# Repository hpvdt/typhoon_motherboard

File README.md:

# Typhoon Motherboard

General template repository for our hardware projects, especially one-off and self-contained projects like custom test equipment. This template assumes that the hardware is being designed in KiCad.

## Organization

Pretty self-explanitory, put hardware related files into the `hardware` folder, firmware in the `firmware` folder. Other folders can be added as needed: for example a `media` folder is handy for storing pictures related to a project which can be used in documentation.

## Conventions

Partly for consistency, partly for functionality; please follow the following conventions:

- Try to keep folder names to single words and all lowercase
- Use underscores to separate words in names (e.g. `board_rev1`). **DO NOT USE SPACES! ESPECIALLY FOR FOLDERS CONTAINING CODE!** Spaces in file paths may cause issues in compilers and such so best to avoid them entirely.

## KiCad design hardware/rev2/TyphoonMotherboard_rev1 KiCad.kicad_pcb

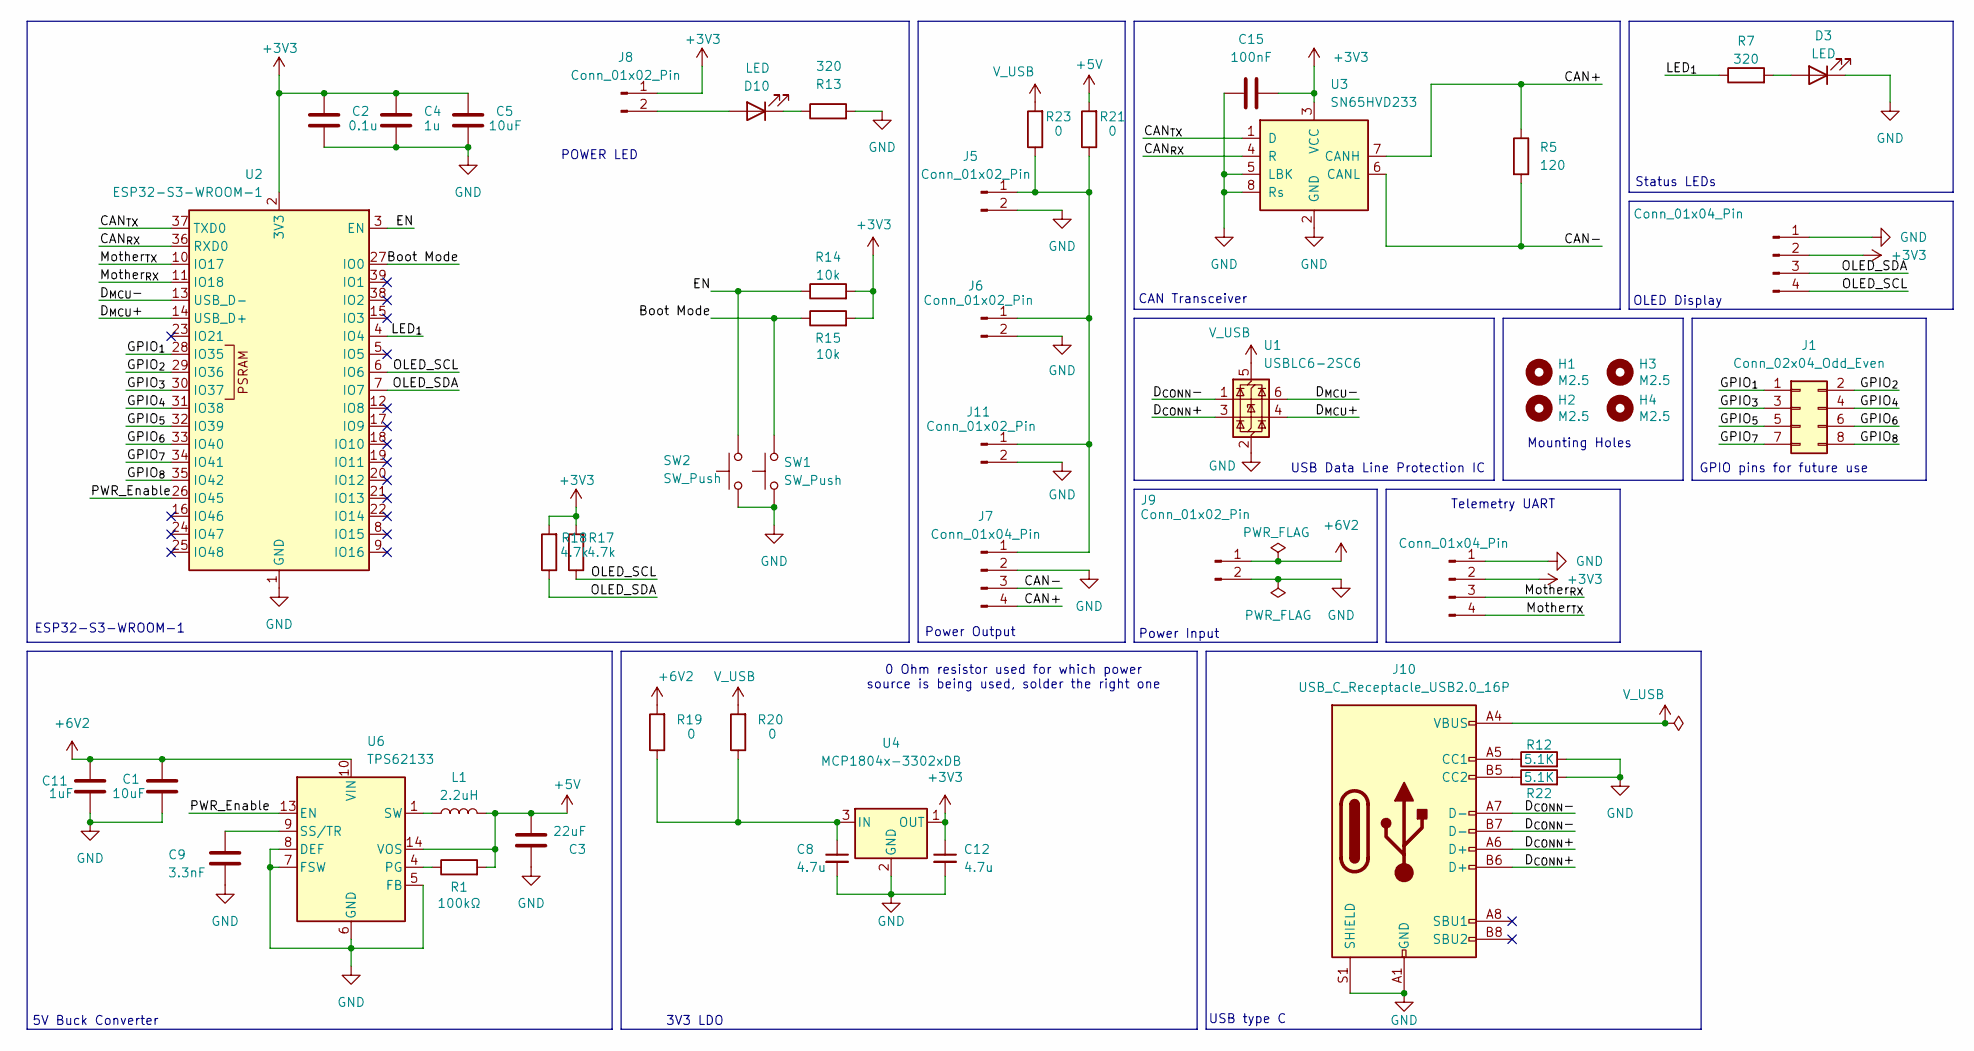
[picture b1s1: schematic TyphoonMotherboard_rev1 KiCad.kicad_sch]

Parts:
C1: 10uF; C_0603_1608Metric
C2: 0.1u; C_0603_1608Metric; Manufacturer Part Number CL10B105KP8NNNC
C3: 22uF; C_0603_1608Metric
C4: 1u; C_0603_1608Metric; Manufacturer Part Number C0603C104K5RACTU
C5: 10uF; C_0603_1608Metric; Manufacturer Part Number CL10A106KQ8NNNC
C8, C12: 4.7u; C_0603_1608Metric; LCSC C1779
C9: 3.3nF; C_0603_1608Metric
C11: 1uF; C_0603_1608Metric
C15: 100nF; C_0603_1608Metric; Manufacturer Part Number CL10E104KC8VPNC
D3, D10: LED; LED_0805_2012Metric; Manufacturer Part Number LTST-C171GKT
H1, H2, H3, H4: M2.5; MountingHole_2.7mm_M2.5
J1: Conn_02x04_Odd_Even; PinSocket_2x04_P2.54mm_Vertical
J2, J4, J7: Conn_01x04_Pin; JST_XH_B4B-XH-A_1x04_P2.50mm_Vertical
J5, J6, J9, J11: Conn_01x02_Pin; JST_XH_B2B-XH-A_1x02_P2.50mm_Vertical
J8: Conn_01x02_Pin; PinHeader_1x02_P2.54mm_Vertical
J10: USB_C_Receptacle_USB2.0_16P; USB_C_Receptacle_JAE_DX07S016JA1R1500; Manufacturer Part Number DX07S016JA3R1500
L1: 2.2uH; L_0805_2012Metric
R1: 100kΩ; R_0603_1608Metric
R5: 120; R_0603_1608Metric
R7: 320; R_0603_1608Metric; Manufacturer Part Number RT0603DRE07320RL
R12, R22: 5.1K; R_0603_1608Metric; Manufacturer Part Number RC0603FR-075K1L
R13: 320; R_0603_1608Metric; Manufacturer Part Number ERA-3AEB331V
R14, R15: 10k; R_0603_1608Metric; Manufacturer Part Number RMCF0603JT10K0
R17, R18: 4.7k; R_0603_1608Metric; Manufacturer Part Number RMCF0603JT10K0
R19, R20, R21, R23: 0; R_1206_3216Metric; Manufacturer Part Number RMCF0603JT10K0
SW1, SW2: SW_Push; SMT_FS
U1: USBLC6-2SC6; SOT-23-6; Manufacturer Part Number USBLC6-2SC6; Digikey Part Number 497-5235-1-ND
U2: ESP32-S3-WROOM-1; Manufacturer Part Number ESP32-S3-WROOM-1-N4R8
U3: SN65HVD233; SOIC-8_3.9x4.9mm_P1.27mm; Manufacturer Part Number SN65HVD233DR
U4: MCP1804x-3302xDB; SOT-223-3_TabPin2
U6: TPS62133; VQFN-16-1EP_3x3mm_P0.5mm_EP1.68x1.68mm_ThermalVias

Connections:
+3V3: C2.1, C4.1, C5.1, C12.1, C15.2, J2.2, J4.2, J8.1, R14.2, R15.2, R17.2, R18.2, U2.2 (3V3), U3.3 (VCC), U4.1 (OUT)
+5V: C3.2, L1.2, R1.2, R21.2, U6.14 (VOS)
+6V2: C1.2, C11.2, J9.1, R19.2, U6.10 (VIN), U6.11 (VIN), U6.12 (VIN)
/Boot Mode: R15.1, SW1.2, U2.27 (IO0)
/CAN+: J7.4, R5.1, U3.7 (CANH)
/CAN-: J7.3, R5.2, U3.6 (CANL)
/CAN_{RX}: U2.36 (RXD0), U3.4 (R)
/CAN_{TX}: U2.37 (TXD0), U3.1 (D)
/D_{CONN}+: J10.A6 (D+), J10.B6 (D+), U1.3 (I/O2)
/D_{CONN}-: J10.A7 (D-), J10.B7 (D-), U1.1 (I/O1)
/D_{MCU}+: U1.4 (I/O2), U2.14 (USB_D+)
/D_{MCU}-: U1.6 (I/O1), U2.13 (USB_D-)
/EN: R14.1, SW2.2, U2.3 (EN)
/GPIO_{1}: J1.1, U2.28 (IO35)
/GPIO_{2}: J1.2, U2.29 (IO36)
/GPIO_{3}: J1.3, U2.30 (IO37)
/GPIO_{4}: J1.4, U2.31 (IO38)
/GPIO_{5}: J1.5, U2.32 (IO39)
/GPIO_{6}: J1.6, U2.33 (IO40)
/GPIO_{7}: J1.7, U2.34 (IO41)
/GPIO_{8}: J1.8, U2.35 (IO42)
/LED_{1}: R7.1, U2.4 (IO4)
/Mother_{RX}: J2.3, U2.11 (IO18)
/Mother_{TX}: J2.4, U2.10 (IO17)
/OLED_SCL: J4.4, R17.1, U2.6 (IO6)
/OLED_SDA: J4.3, R18.1, U2.7 (IO7)
/PWR_Enable: U2.26 (IO45), U6.13 (EN)
GND: C1.1, C2.2, C3.1, C4.2, C5.2, C8.2, C9.1, C11.1, C12.2, C15.1, D3.1 (K), J2.1, J4.1, J5.2, J6.2, J7.2, J9.2, J10.A1 (GND), J10.A12 (GND), J10.B1 (GND), J10.B12 (GND), J10.S1 (SHIELD), J11.2, R12.2, R13.2, R22.2, SW1.1, SW2.1, U1.2 (GND), U2.1 (GND), U2.40 (GND), U2.41 (GND), U3.2 (GND), U3.5 (LBK), U3.8 (Rs), U4.2 (GND), U6.5 (FB), U6.6 (GND), U6.7 (FSW), U6.8 (DEF), U6.15 (GND), U6.16 (GND), U6.17 (GND)
unnamed: D3.2 (A), R7.2
unnamed: D10.2 (A), J8.2
unnamed: D10.1 (K), R13.1
unnamed: J10.A5 (CC1), R12.1
unnamed: J10.B5 (CC2), R22.1
unnamed: J5.1, J6.1, J7.1, J11.1, R21.1, R23.1
unnamed: L1.1, U6.1 (SW), U6.2 (SW), U6.3 (SW)
unnamed: C8.1, R19.1, R20.1, U4.3 (IN)
unnamed: R1.1, U6.4 (PG)
unnamed: C9.2, U6.9 (SS/TR)
V_USB: J10.A4 (VBUS), J10.A9 (VBUS), J10.B4 (VBUS), J10.B9 (VBUS), R20.2, R23.2, U1.5 (VBUS)

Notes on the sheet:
Status LEDs
Power Input
ESP32-S3-WROOM-1
USB Data Line Protection IC
CAN Transceiver
5V Buck Converter
3V3 LDO
OLED Display
GPIO pins for future use
Mounting Holes
Power Output
POWER LED
0 Ohm resistor used for which power source is being used, solder the right one
USB type C
Telemetry UART

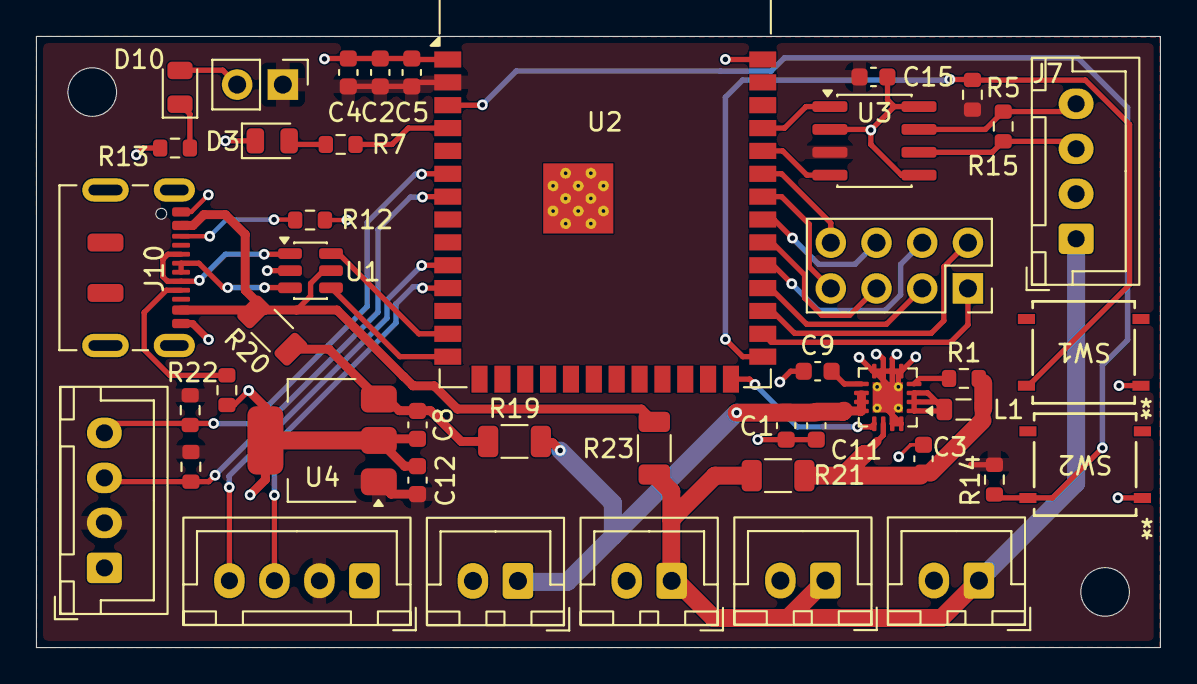
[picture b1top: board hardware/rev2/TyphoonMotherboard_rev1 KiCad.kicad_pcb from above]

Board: 2 copper layers, 62.4 x 33.9 mm, 48 parts (0 on the bottom side), 39 nets.

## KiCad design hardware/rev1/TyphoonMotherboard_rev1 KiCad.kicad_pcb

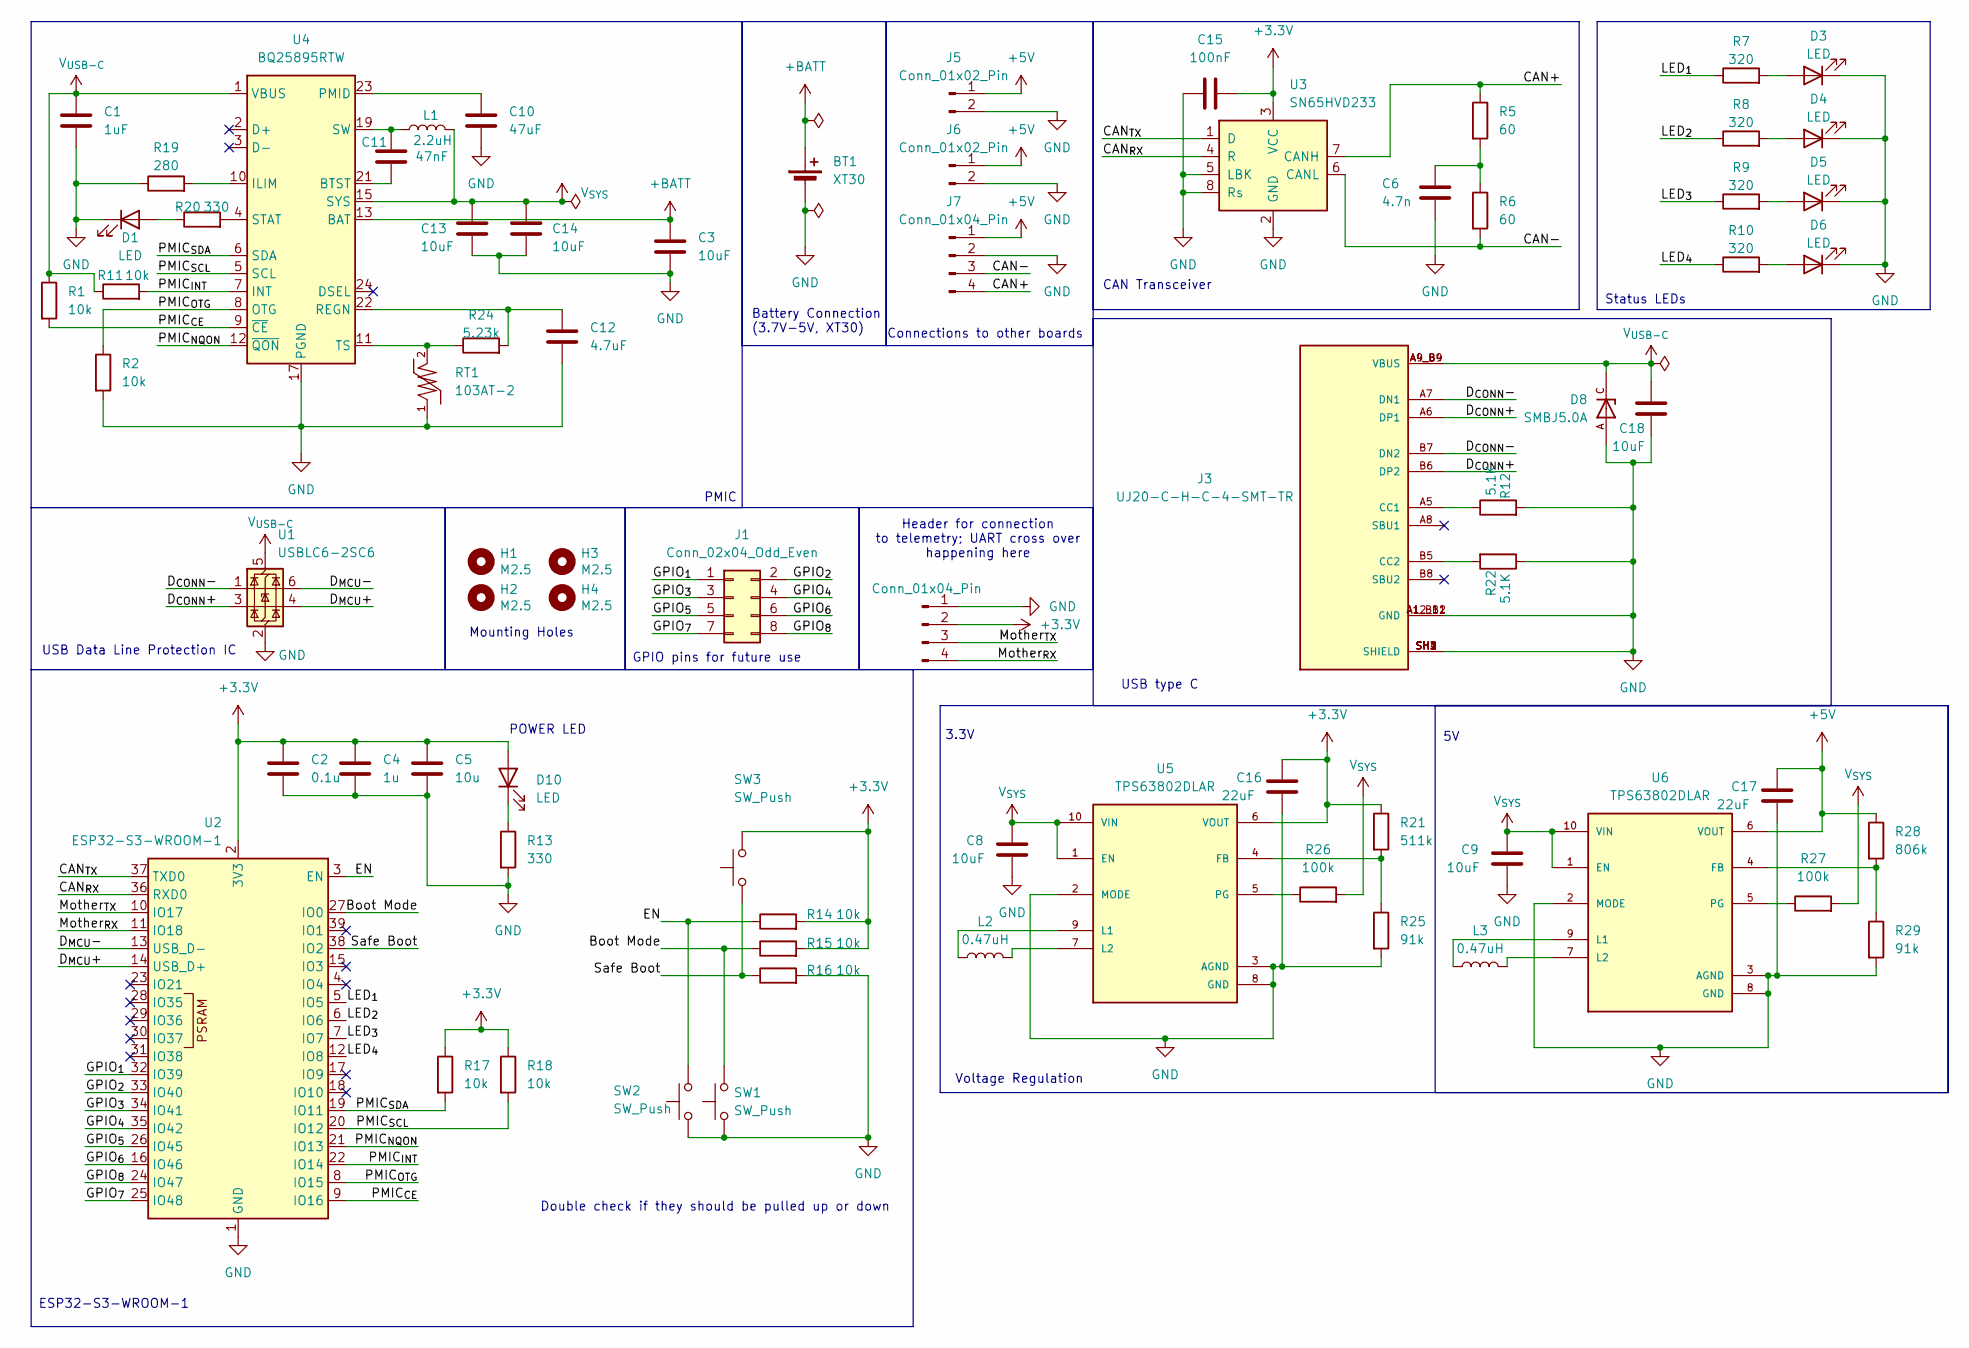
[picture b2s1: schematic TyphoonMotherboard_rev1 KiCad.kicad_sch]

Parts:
BT1: XT30; AMASS_XT30U-F_1x02_P5.0mm_Vertical
C1: 1uF; C_0603_1608Metric
C2: 0.1u; C_0603_1608Metric
C3, C8, C9, C13, C14, C18: 10uF; C_0603_1608Metric
C4: 1u; C_0603_1608Metric
C5: 10u; C_0603_1608Metric
C6: 4.7n; C_0603_1608Metric
C10: 47uF; C_0603_1608Metric
C11: 47nF; C_0603_1608Metric
C12: 4.7uF; C_0603_1608Metric
C15: 100nF; C_0603_1608Metric
C16, C17: 22uF; C_0603_1608Metric
D1, D3, D4, D5, D6, D10: LED; LED_0805_2012Metric
D8: SMBJ5.0A; DIOM4336X265N; PARTREV F2102
H1, H2, H3, H4: M2.5; MountingHole_2.7mm_M2.5
J1: Conn_02x04_Odd_Even; PinSocket_2x04_P2.54mm_Vertical
J2, J7: Conn_01x04_Pin; JST_XH_B4B-XH-A_1x04_P2.50mm_Vertical
J3: UJ20-C-H-C-4-SMT-TR; CUI_UJ20-C-H-C-4-SMT-TR; PARTREV 1.0
J5, J6: Conn_01x02_Pin; JST_XH_B2B-XH-A_1x02_P2.50mm_Vertical
L1: 2.2uH; L_0805_2012Metric
L2, L3: 0.47uH; L_0603_1608Metric
R1, R2, R11, R14, R15, R16, R17, R18: 10k; R_0603_1608Metric
R5, R6: 60; R_0603_1608Metric
R7, R8, R9, R10: 320; R_0603_1608Metric
R12, R22: 5.1K; R_0603_1608Metric
R13, R20: 330; R_0603_1608Metric
R19: 280; R_0603_1608Metric
R21: 511k; R_0603_1608Metric
R24: 5.23k; R_0603_1608Metric
R25, R29: 91k; R_0603_1608Metric
R26, R27: 100k; R_0603_1608Metric
R28: 806k; R_0603_1608Metric
RT1: 103AT-2
SW1, SW2, SW3: SW_Push; PinHeader_1x02_P2.54mm_Vertical
U1: USBLC6-2SC6; SOT-23-6
U2: ESP32-S3-WROOM-1
U3: SN65HVD233; SOIC-8_3.9x4.9mm_P1.27mm
U4: BQ25895RTW; Texas_RTW_WQFN-24-1EP_4x4mm_P0.5mm_EP2.7x2.7mm_ThermalVias
U5, U6: TPS63802DLAR; VREG_TPS63802DLAR; PARTREV B; DigiKey_Part_Number 296-TPS63802DLARTR-ND

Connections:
+3.3V: C2.1, C4.1, C5.1, C15.2, C16.1, D10.2 (A), J2.2, R14.2, R15.2, R17.1, R18.1, R21.1, SW3.2, U2.2 (3V3), U3.3 (VCC), U5.6 (VOUT)
+5V: C17.1, J5.1, J6.1, J7.1, R28.1, U6.6 (VOUT)
+BATT: BT1.1 (+), C3.1, U4.13 (BAT), U4.14 (BAT)
/Boot Mode: R15.1, SW1.2, U2.27 (IO0)
/CAN+: J7.4, R5.1, U3.7 (CANH)
/CAN-: J7.3, R6.2, U3.6 (CANL)
/CAN_{RX}: U2.36 (RXD0), U3.4 (R)
/CAN_{TX}: U2.37 (TXD0), U3.1 (D)
/D_{CONN}+: J3.A6 (DP1), J3.B6 (DP2), U1.3 (I/O2)
/D_{CONN}-: J3.A7 (DN1), J3.B7 (DN2), U1.1 (I/O1)
/D_{MCU}+: U1.4 (I/O2), U2.14 (USB_D+)
/D_{MCU}-: U1.6 (I/O1), U2.13 (USB_D-)
/EN: R14.1, SW2.2, U2.3 (EN)
/GPIO_{1}: J1.1, U2.32 (IO39)
/GPIO_{2}: J1.2, U2.33 (IO40)
/GPIO_{3}: J1.3, U2.34 (IO41)
/GPIO_{4}: J1.4, U2.35 (IO42)
/GPIO_{5}: J1.5, U2.26 (IO45)
/GPIO_{6}: J1.6, U2.16 (IO46)
/GPIO_{7}: J1.7, U2.25 (IO48)
/GPIO_{8}: J1.8, U2.24 (IO47)
/LED_{1}: R7.1, U2.5 (IO5)
/LED_{2}: R8.1, U2.6 (IO6)
/LED_{3}: R9.1, U2.7 (IO7)
/LED_{4}: R10.1, U2.12 (IO8)
/Mother_{RX}: J2.4, U2.11 (IO18)
/Mother_{TX}: J2.3, U2.10 (IO17)
/PMIC_{CE}: R1.2, U2.9 (IO16), U4.9 (~CE)
/PMIC_{INT}: R11.2, U2.22 (IO14), U4.7 (INT)
/PMIC_{NQON}: U2.21 (IO13), U4.12 (~QON)
/PMIC_{OTG}: R2.1, U2.8 (IO15), U4.8 (OTG)
/PMIC_{SCL}: R18.2, U2.20 (IO12), U4.5 (SCL)
/PMIC_{SDA}: R17.2, U2.19 (IO11), U4.6 (SDA)
/Safe Boot: R16.1, SW3.1, U2.38 (IO2)
GND: BT1.2 (-), C1.2, C2.2, C3.2, C4.2, C5.2, C6.2, C8.2, C9.2, C10.2, C12.2, C13.2, C14.2, C15.1, C16.2, C17.2, C18.2, D1.1 (K), D3.1 (K), D4.1 (K), D5.1 (K), D6.1 (K), D8.A, J2.1, J3.A1_B12 (GND), J3.A12_B1 (GND), J3.SH1 (SHIELD), J3.SH2 (SHIELD), J3.SH3 (SHIELD), J3.SH4 (SHIELD), J5.2, J6.2, J7.2, R2.2, R12.2, R13.2, R16.2, R19.1, R22.1, R25.2, R29.2, RT1.1, SW1.1, SW2.1, U1.2 (GND), U2.1 (GND), U2.40 (GND), U2.41 (GND), U3.2 (GND), U3.5 (LBK), U3.8 (Rs), U4.17 (PGND), U4.18 (PGND), U4.25 (PGND), U5.2 (MODE), U5.3 (AGND), U5.8 (GND), U6.2 (MODE), U6.3 (AGND), U6.8 (GND)
unnamed: C6.1, R5.2, R6.1
unnamed: C11.1, L1.1, U4.19 (SW), U4.20 (SW)
unnamed: D1.2 (A), R20.1
unnamed: D3.2 (A), R7.2
unnamed: D4.2 (A), R8.2
unnamed: D5.2 (A), R9.2
unnamed: D6.2 (A), R10.2
unnamed: D10.1 (K), R13.1
unnamed: J3.A5 (CC1), R12.1
unnamed: J3.B5 (CC2), R22.2
unnamed: C11.2, U4.21 (BTST)
unnamed: R19.2, U4.10 (ILIM)
unnamed: C10.1, U4.23 (PMID)
unnamed: C12.1, R24.2, U4.22 (REGN)
unnamed: R20.2, U4.4 (STAT)
unnamed: R24.1, RT1.2, U4.11 (TS)
unnamed: R21.2, R25.1, U5.4 (FB)
unnamed: L2.1, U5.9 (L1)
unnamed: L2.2, U5.7 (L2)
unnamed: R26.1, U5.5 (PG)
unnamed: R28.2, R29.1, U6.4 (FB)
unnamed: L3.1, U6.9 (L1)
unnamed: L3.2, U6.7 (L2)
unnamed: R27.1, U6.5 (PG)
V_{SYS}: C8.1, C9.1, C13.1, C14.1, L1.2, R26.2, R27.2, U4.15 (SYS), U4.16 (SYS), U5.1 (EN), U5.10 (VIN), U6.1 (EN), U6.10 (VIN)
V_{USB-C}: C1.1, C18.1, D8.C, J3.A4_B9 (VBUS), J3.A9_B4 (VBUS), R1.1, R11.1, U1.5 (VBUS), U4.1 (VBUS)

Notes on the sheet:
PMIC
Status LEDs
ESP32-S3-WROOM-1
USB Data Line Protection IC
CAN Transceiver
Voltage Regulation
3.3V
Battery Connection (3.7V-5V, XT30)
GPIO pins for future use
Mounting Holes
Connections to other boards
POWER LED
Double check if they should be pulled up or down
USB type C
Header for connection to telemetry; UART cross over happening here

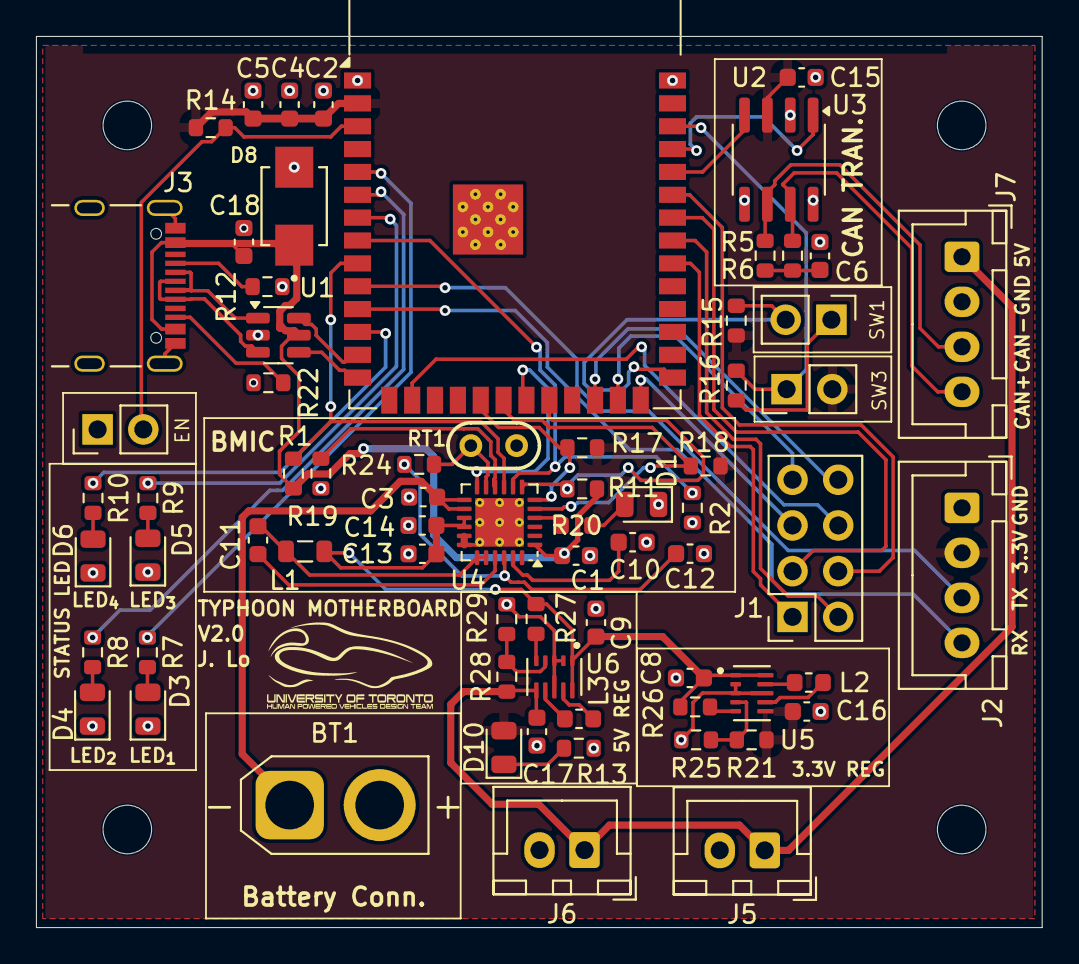
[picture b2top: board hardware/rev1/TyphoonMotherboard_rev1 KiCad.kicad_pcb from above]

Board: 2 copper layers, 55.9 x 49.5 mm, 74 parts (0 on the bottom side), 61 nets.

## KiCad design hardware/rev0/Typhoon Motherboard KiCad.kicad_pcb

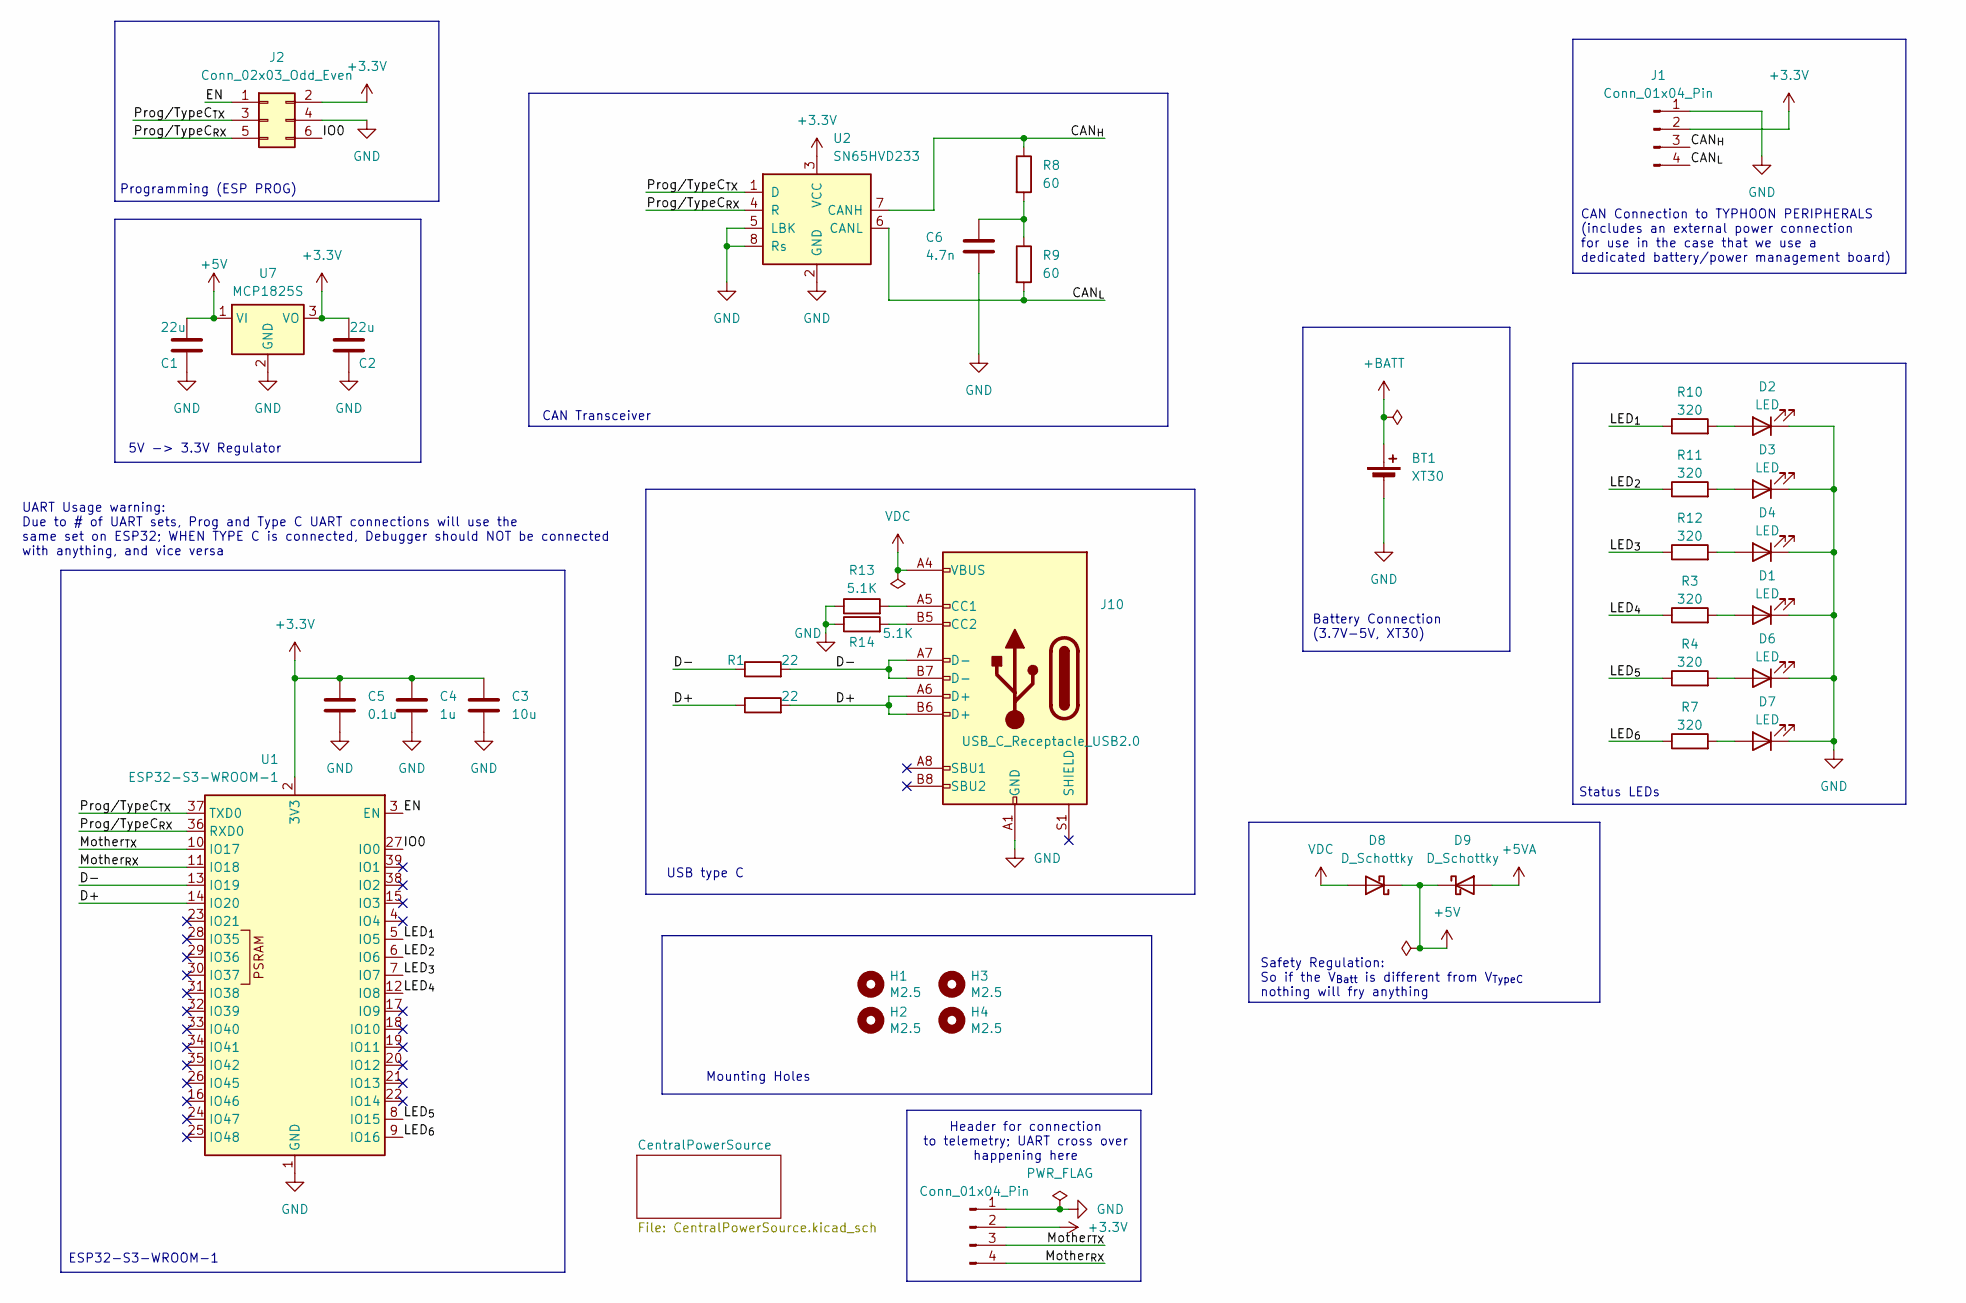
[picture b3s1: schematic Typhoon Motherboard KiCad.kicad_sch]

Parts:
BT1: XT30; AMASS_XT30PW-M_1x02_P2.50mm_Horizontal
C1, C2: 22u; C_0603_1608Metric
C3: 10u; C_0603_1608Metric
C4: 1u; C_0603_1608Metric
C5: 0.1u; C_0603_1608Metric
C6: 4.7n; C_0603_1608Metric
D1, D2, D3, D4, D6, D7: LED; LED_0805_2012Metric
D8, D9: D_Schottky; D_SOD-123
H1, H2, H3, H4: M2.5; MountingHole_2.7mm_M2.5
J1: Conn_01x04_Pin; JST_EH_S4B-EH_1x04_P2.50mm_Horizontal
J2: Conn_02x03_Odd_Even; IDC-Header_2x03_P2.54mm_Vertical
J3: Conn_01x04_Pin; PinHeader_1x04_P1.27mm_Vertical
J10: USB_C_Receptacle_USB2.0; USB_C_Receptacle_HRO_TYPE-C-31-M-12
R1, R2: 22; R_0603_1608Metric
R3, R4, R7, R10, R11, R12: 320; R_0603_1608Metric
R8, R9: 60; R_0603_1608Metric
R13, R14: 5.1K; R_0603_1608Metric
U1: ESP32-S3-WROOM-1
U2: SN65HVD233; SOIC-8_3.9x4.9mm_P1.27mm
U7: MCP1825S; SOT-223-3_TabPin2

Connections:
+3.3V: C2.2, C3.1, C4.1, C5.1, J1.2, J2.2, J3.2, U1.2 (3V3), U2.3 (VCC), U7.3 (VO)
+5V: C1.2, D8.1 (K), D9.1 (K), U7.1 (VI)
+5VA: D9.2 (A); also elsewhere on the board
+BATT: BT1.1 (+); also elsewhere on the board
/CAN_{H}: J1.3, R8.1, U2.7 (CANH)
/CAN_{L}: J1.4, R9.2, U2.6 (CANL)
/EN: J2.1, U1.3 (EN)
/IO0: J2.6, U1.27 (IO0)
/LED_{1}: R10.1, U1.5 (IO5)
/LED_{2}: R11.1, U1.6 (IO6)
/LED_{3}: R12.1, U1.7 (IO7)
/LED_{4}: R3.1, U1.12 (IO8)
/LED_{5}: R4.1, U1.8 (IO15)
/LED_{6}: R7.1, U1.9 (IO16)
/Mother_{RX}: J3.4, U1.11 (IO18)
/Mother_{TX}: J3.3, U1.10 (IO17)
/Prog/TypeC_{RX}: J2.5, U1.36 (RXD0), U2.4 (R)
/Prog/TypeC_{TX}: J2.3, U1.37 (TXD0), U2.1 (D)
GND: BT1.2 (-), C1.1, C2.1, C3.2, C4.2, C5.2, C6.2, D1.1 (K), D2.1 (K), D3.1 (K), D4.1 (K), D6.1 (K), D7.1 (K), J1.1, J2.4, J3.1, J10.A1 (GND), J10.A12 (GND), J10.B1 (GND), J10.B12 (GND), R13.1, R14.1, U1.1 (GND), U1.40 (GND), U1.41 (GND), U2.2 (GND), U2.5 (LBK), U2.8 (Rs), U7.2 (GND); also elsewhere on the board
unnamed: C6.1, R8.2, R9.1
unnamed: D1.2 (A), R3.2
unnamed: D2.2 (A), R10.2
unnamed: D3.2 (A), R11.2
unnamed: D4.2 (A), R12.2
unnamed: D6.2 (A), R4.2
unnamed: D7.2 (A), R7.2
unnamed: J10.A5 (CC1), R13.2
unnamed: J10.B5 (CC2), R14.2
VDC: D8.2 (A), J10.A4 (VBUS), J10.A9 (VBUS), J10.B4 (VBUS), J10.B9 (VBUS)

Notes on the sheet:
Header for connection to telemetry; UART cross over happening here
Battery Connection (3.7V-5V, XT30)
Programming (ESP PROG)
Status LEDs
CAN Connection to TYPHOON PERIPHERALS (includes an external power connection for use in the case that we use a dedicated battery/power management board)
Safety Regulation: So if the V_{Batt} is different from V_{TypeC} nothing will fry anything
Mounting Holes
5V -> 3.3V Regulator
USB type C
ESP32-S3-WROOM-1
CAN Transceiver
UART Usage warning: Due to # of UART sets, Prog and Type C UART connections will use the same set on ESP32; WHEN TYPE C is connected, Debugger should NOT be connected with anything, and vice versa

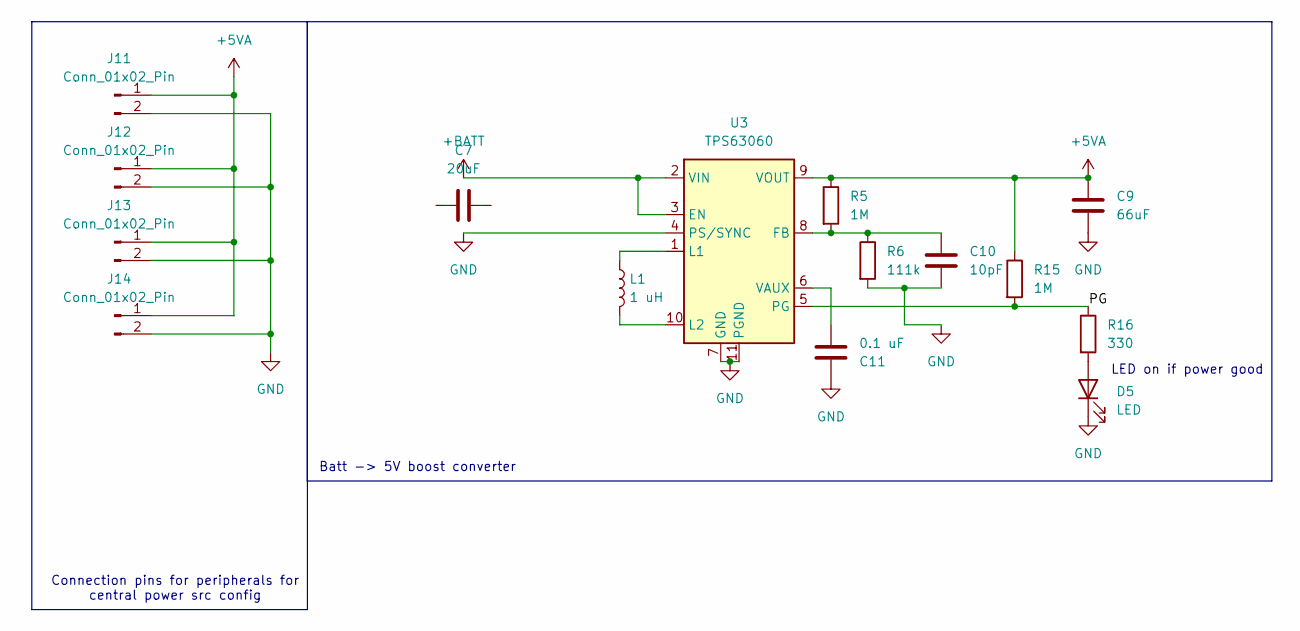
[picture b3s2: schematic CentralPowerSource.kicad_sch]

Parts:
C7: 20uF; C_0603_1608Metric
C9: 66uF; C_0603_1608Metric
C10: 10pF; C_0603_1608Metric
C11: 0.1 uF; C_0603_1608Metric
D5: LED; LED_0805_2012Metric
J11, J12, J13, J14: Conn_01x02_Pin; JST_EH_S2B-EH_1x02_P2.50mm_Horizontal
L1: 1 uH; L_0805_2012Metric
R5, R15: 1M; R_0603_1608Metric
R6: 111k; R_0603_1608Metric
R16: 330; R_0603_1608Metric
U3: TPS63060; Texas_S-PWSON-N10_ThermalVias

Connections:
+5VA: C9.1, J11.1, J12.1, J13.1, J14.1, R5.1, R15.1, U3.9 (VOUT); also elsewhere on the board
+BATT: U3.2 (VIN), U3.3 (EN); also elsewhere on the board
/CentralPowerSource/PG: R15.2, R16.1, U3.5 (PG)
GND: C9.2, C10.2, C11.1, D5.1 (K), J11.2, J12.2, J13.2, J14.2, R6.2, U3.4 (PS/SYNC), U3.7 (GND), U3.11 (PGND); also elsewhere on the board
unnamed: D5.2 (A), R16.2
unnamed: C10.1, R5.2, R6.1, U3.8 (FB)
unnamed: L1.1, U3.1 (L1)
unnamed: L1.2, U3.10 (L2)
unnamed: C11.2, U3.6 (VAUX)

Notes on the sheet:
Batt -> 5V boost converter
Connection pins for peripherals for central power src config
LED on if power good

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
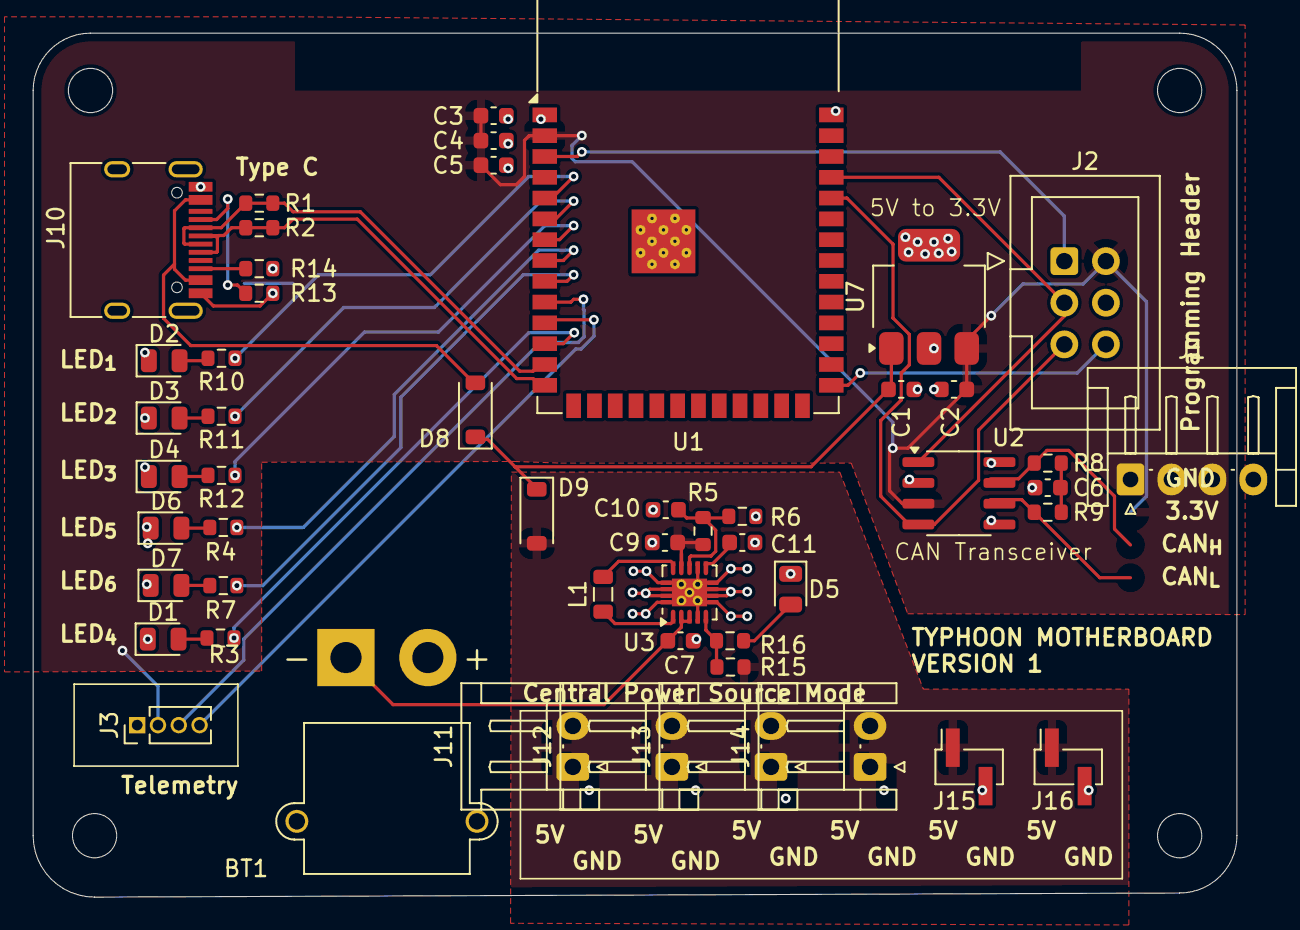
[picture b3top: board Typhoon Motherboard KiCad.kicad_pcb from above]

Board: 2 copper layers, 73.5 x 52.8 mm, 55 parts (0 on the bottom side), 39 nets.

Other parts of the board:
J15, J16: Conn_01x02_Pin; PinHeader_1x02_P2.00mm_Vertical_SMD_Pin1Right

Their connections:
+5VA: J15.1, J16.1; also elsewhere on the board
GND: J15.2, J16.2; also elsewhere on the board

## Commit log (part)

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2024-07-12 coped files from old typhoon electronics repo into this new repo which is dedicated to only typhoon motherboard
2024-07-28 first version of motherboard schematic
2024-07-28 added to do list in the schematic notes lol
2024-07-28 added notes
2024-07-31 Rev 2 upload
2024-07-31 revision 1 by savo
2024-07-31 create new sheet; update USBC
    created new sheet for the central power source configuration so it's more organized; updated the USB-C symbol; added in safety regulations (diodes) to prevent conflict in voltages
2024-08-01 Everything written in the schematic
2024-09-04 Update Schematics and Start PCB
2024-09-04 First draft of PCB
2024-09-05 Finalized First Draft of the PCB
2024-09-05 Fixed Placement issues (aesthetic fixes)
2024-09-06 Update (Round Edges)
2024-09-07 Added mounting holes
2024-10-05 Updated header (NOT FINAL)
2024-10-08 Final Edit
2024-10-31 Updated the Boost Converter
2024-11-17 Production Files
2025-02-17 Updated Rev 1
2025-02-27 Updated Voltage Regulation
2025-05-27 Rev1 Fully Finalized
2025-05-27 Firmware shit
2025-09-10 firmware changes
2026-01-11 Blinky Example Creation
2026-01-13 Deleted Unused files
2026-01-22 Updated the Symbol Fields for Motherboard
2026-01-24 Added inital code for CAN loopback test
2026-02-10 Matched the CAN test to STM32 (speed and cadence) instead of Loopback
2026-03-24 rev2 for new revision
2026-03-25 worked on pmic schematic
2026-03-29 pmic and voltage regulator schematic updates
2026-04-07 Reviewed the Schematic making PCB
2026-05-16 removed updates
2026-05-19 Updated rev2 voltage regulation schematic (TP62133 regulator)
2026-05-19 Finished Schematic Ready for PCB Design
2026-05-19 some other small changes
2026-06-06 <UPDATE> Oliver Review Ver
